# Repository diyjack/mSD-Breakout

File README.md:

# mSD-Breakout
Breakout with microSD socket and level shifter.

## Shop
* [mSD-Breakout](http://www.watterott.com/en/mSD-Breakout)

## Features
* microSD socket (SPI) support SD and SDHC cards (up to 32GB)
* 5V tolerant inputs (level shifter)
* on-board 3.3V voltage regulator

## Hardware and Software
* [Schematics + Layout](https://github.com/watterott/mSD-Breakout/tree/master/pcb)

* Arduino Uno Connection (Example Sketch: ```File->Examples->SD->CardInfo```):
    ```
    Uno -> Breakout
    ---------------
    5V  -> 5V
    GND -> GND
    D13 -> CLK
    D12 -> DO (MISO)
    D11 -> DI (MOSI)
    D4  -> CS
    ```

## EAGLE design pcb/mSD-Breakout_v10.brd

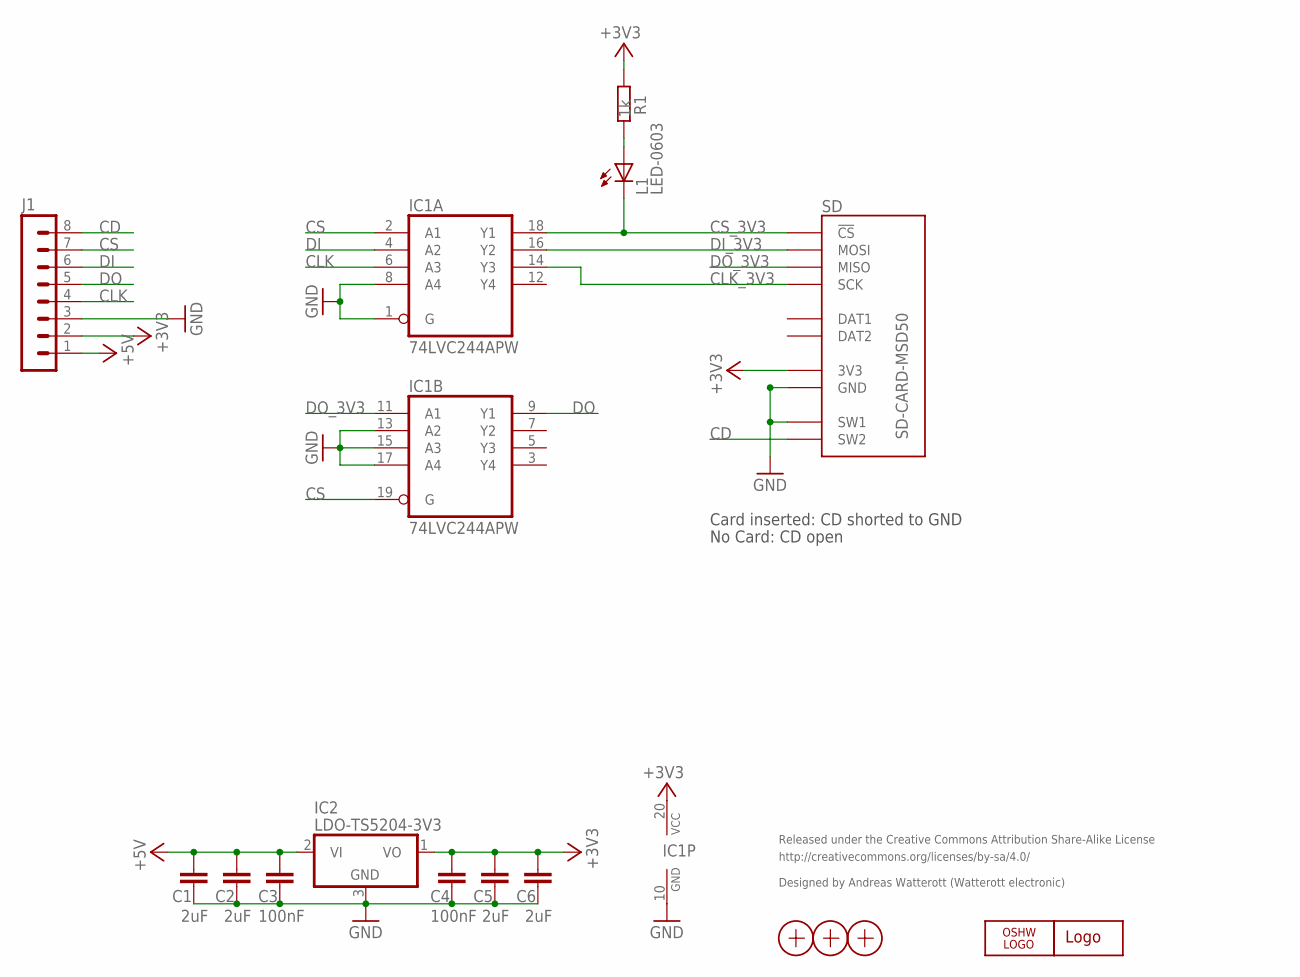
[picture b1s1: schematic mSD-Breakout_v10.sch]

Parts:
C1, C2, C5, C6: 2uF; C0603
C3, C4: 100nF; C0603
IC1: 74LVC244APW; TSSOP20
IC2: LDO-TS5204-3V3; SOT23
J1: MA08-1
L1: LED-0603; LED_0603
LOGO1: OSHW_LOGOX0100; OSHW_6X100
LOGO2: LOGO-SPARK_PLACE; SPARK_TPLACE
R1: 1k; R0603
SD: SD-CARD-MSD50; SD_5031821853
X1, X2, X3: PASSER

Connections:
+3V3: C4.1, C5.1, C6.1, IC1.20 (VCC), IC2.1 (VO), J1.2, R1.1, SD.VCC (3V3)
+5V: C1.1, C2.1, C3.1, IC2.2 (VI), J1.1
CD: J1.8, SD.SW2
CLK: IC1.6 (A3), J1.4
CLK_3V3: IC1.14 (Y3), SD.SCK
CS: IC1.2 (A1), IC1.19 (G), J1.7
CS_3V3: IC1.18 (Y1), L1.C, SD.CS (!CS)
DI: IC1.4 (A2), J1.6
DI_3V3: IC1.16 (Y2), SD.MOSI
DO: IC1.9 (Y1), J1.5
DO_3V3: IC1.11 (A1), SD.MISO
GND: C1.2, C2.2, C3.2, C4.2, C5.2, C6.2, IC1.1 (G), IC1.8 (A4), IC1.10 (GND), IC1.13 (A2), IC1.15 (A3), IC1.17 (A4), IC2.3 (GND), J1.3, SD.GND, SD.SW1
unnamed: L1.A, R1.2

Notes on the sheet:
Released under the Creative Commons Attribution Share-Alike License
http://creativecommons.org/licenses/by-sa/4.0/
Designed by Andreas Watterott (Watterott electronic)
Card inserted: CD shorted to GND
No Card: CD open

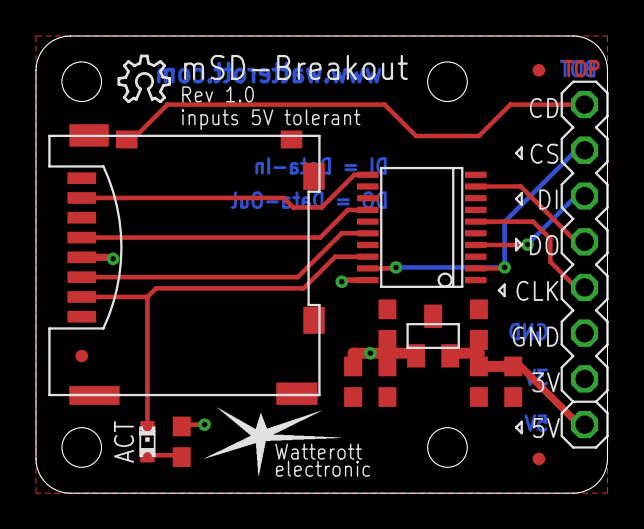
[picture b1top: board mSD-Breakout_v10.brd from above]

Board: 2 copper layers, 31.8 x 25.4 mm, 17 parts (0 on the bottom side), 13 nets.

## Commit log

2014-04-13 added schematic and layout files
2014-04-13 added readme
2014-04-17 added image
2014-05-24 updated schematics
2014-08-15 updated schematic and layout files
2014-08-21 updated layout and schematics
2014-11-06 cleaned up schematics and layout
2015-01-11 moved image
